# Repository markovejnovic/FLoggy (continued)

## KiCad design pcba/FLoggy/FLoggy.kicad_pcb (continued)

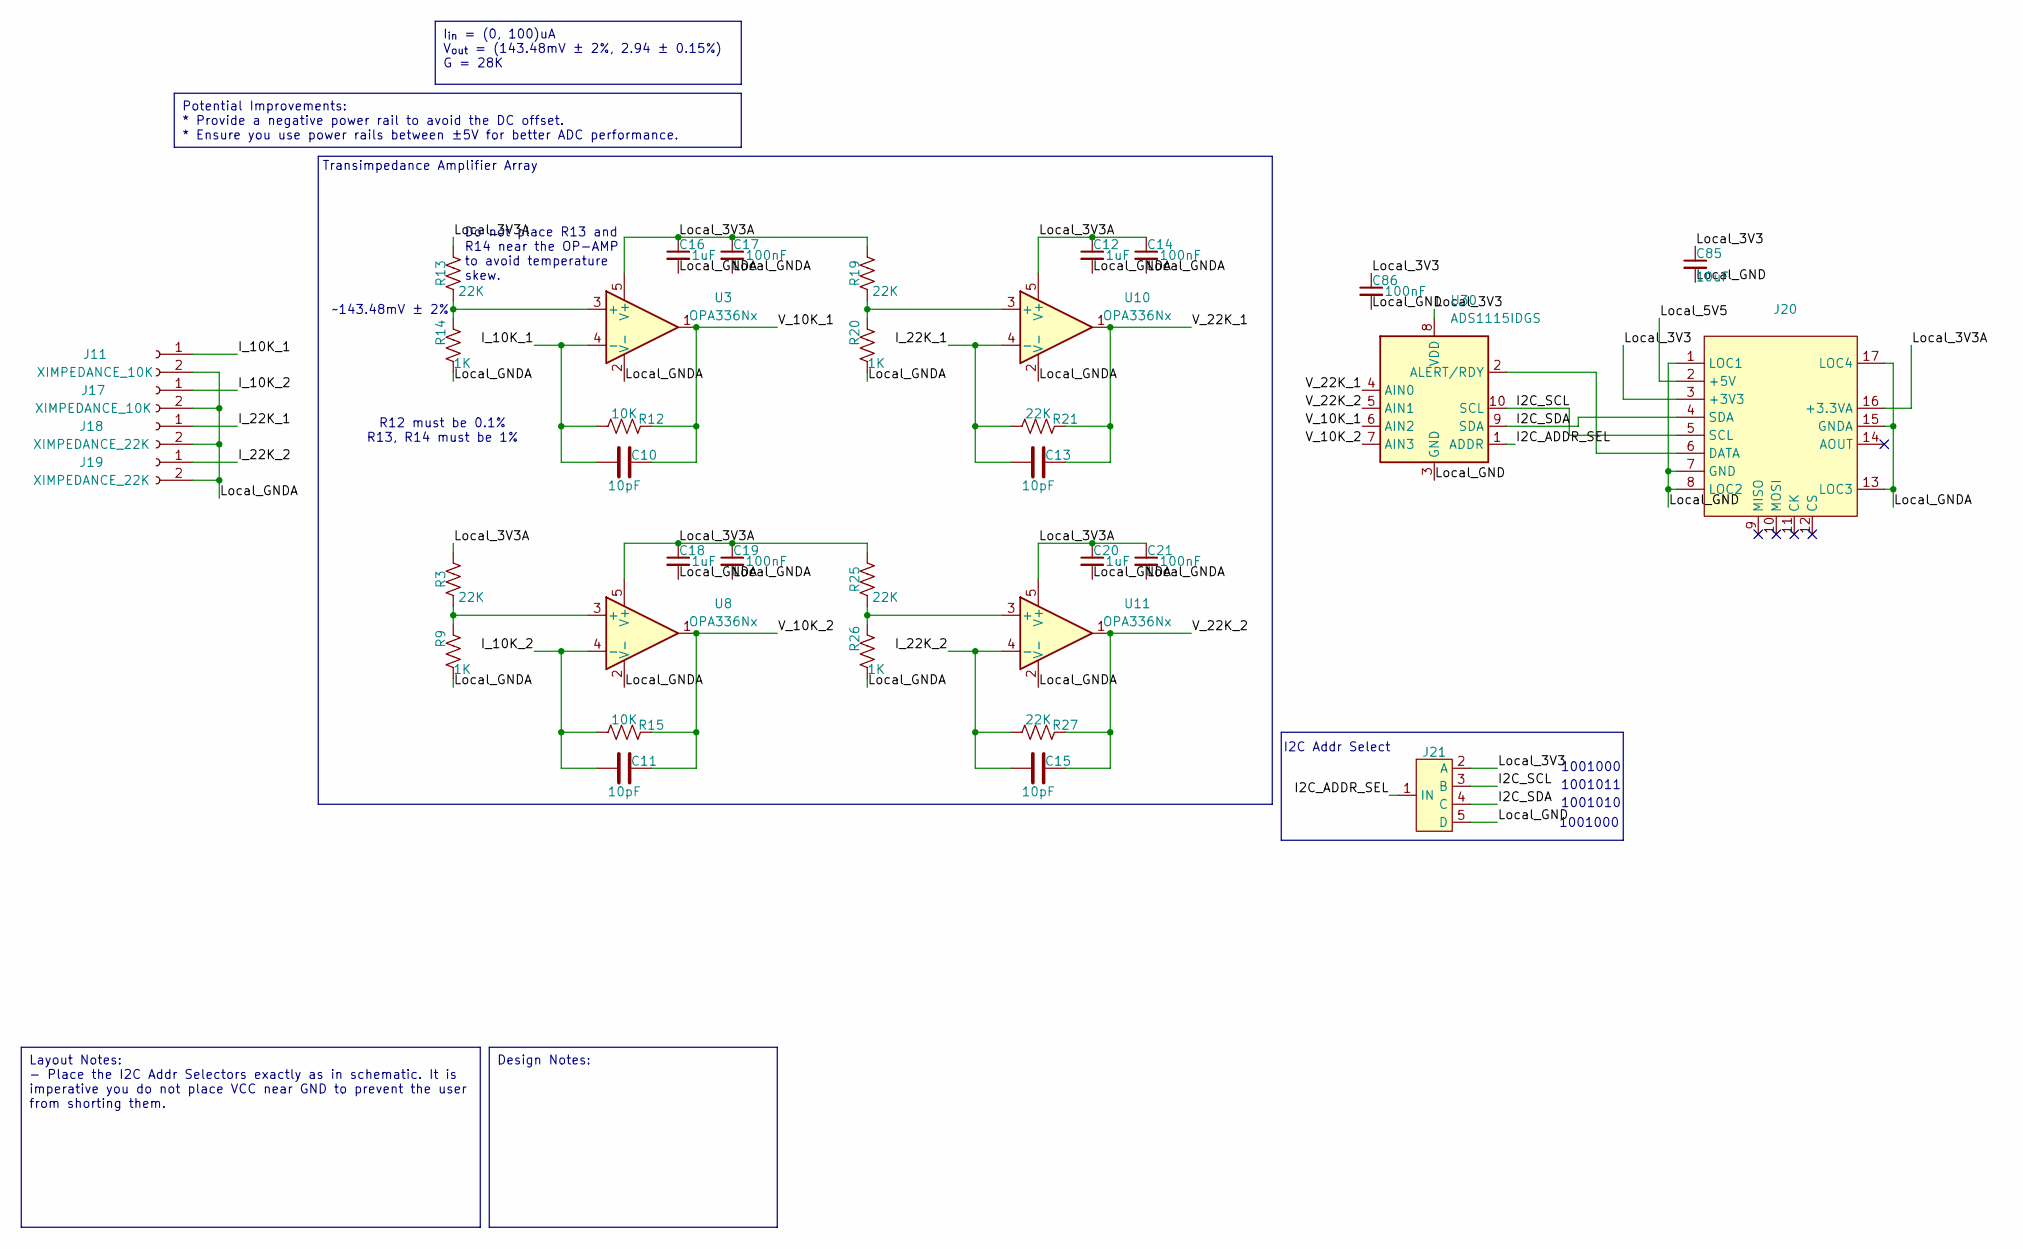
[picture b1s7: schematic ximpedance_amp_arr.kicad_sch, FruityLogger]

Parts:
C10, C11, C13, C15: 10pF; C_0603_1608Metric; JLCPCB Basic? True
C12, C16, C18, C20: 1uF; C_0805_2012Metric; JLCPCB Basic? True
C14, C17, C19, C21, C86: 100nF; C_0603_1608Metric; JLCPCB Basic? True
C85: 10uF; C_0805_2012Metric; JLCPCB Basic? True
J11, J17: XIMPEDANCE_10K; TerminalBlock_Phoenix_MPT-0,5-2-2.54_1x02_P2.54mm_Horizontal
J18, J19: XIMPEDANCE_22K; TerminalBlock_Phoenix_MPT-0,5-2-2.54_1x02_P2.54mm_Horizontal
J20: FloggyModuleShield
J21: I2C Addr Picker
R3, R13, R19, R21, R25, R27: 22K; R_0603_1608Metric; JLCPCB Basic? True
R9, R14, R20, R26: 1K; R_0603_1608Metric; JLCPCB Basic? True
R12, R15: 10K; R_0603_1608Metric; JLCPCB Basic? True
U3, U8, U10, U11: OPA336Nx; SOT-23-5; JLCPCB Basic? False
U30: ADS1115IDGS; TSSOP-10_3x3mm_P0.5mm

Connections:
/Transimpedance Amplifier Array Breakout/I2C_ADDR_SEL: J21.1 (IN), U30.1 (ADDR)
/Transimpedance Amplifier Array Breakout/I2C_SCL: J20.5 (SCL), J21.3 (B), U30.10 (SCL)
/Transimpedance Amplifier Array Breakout/I2C_SDA: J20.4 (SDA), J21.4 (C), U30.9 (SDA)
/Transimpedance Amplifier Array Breakout/I_10K_1: C10.1, J11.1, R12.1, U3.4 (-)
/Transimpedance Amplifier Array Breakout/I_10K_2: C11.1, J17.1, R15.1, U8.4 (-)
/Transimpedance Amplifier Array Breakout/I_22K_1: C13.1, J18.1, R21.1, U10.4 (-)
/Transimpedance Amplifier Array Breakout/I_22K_2: C15.1, J19.1, R27.1, U11.4 (-)
/Transimpedance Amplifier Array Breakout/Local_3V3: C85.1, C86.1, J20.3 (+3V3), J21.2 (A), U30.8 (VDD)
/Transimpedance Amplifier Array Breakout/Local_3V3A: C12.1, C14.1, C16.1, C17.1, C18.1, C19.1, C20.1, C21.1, J20.16 (+3.3VA), R3.2, R13.2, R19.2, R25.2, U3.5 (V+), U8.5 (V+), U10.5 (V+), U11.5 (V+)
/Transimpedance Amplifier Array Breakout/Local_5V5: J20.2 (+5V)
/Transimpedance Amplifier Array Breakout/Local_GND: C85.2, C86.2, J20.1 (LOC1), J20.7 (GND), J20.8 (LOC2), J21.5 (D), U30.3 (GND)
/Transimpedance Amplifier Array Breakout/Local_GNDA: C12.2, C14.2, C16.2, C17.2, C18.2, C19.2, C20.2, C21.2, J11.2, J17.2, J18.2, J19.2, J20.13 (LOC3), J20.15 (GNDA), J20.17 (LOC4), R9.1, R14.1, R20.1, R26.1, U3.2 (V-), U8.2 (V-), U10.2 (V-), U11.2 (V-)
/Transimpedance Amplifier Array Breakout/V_10K_1: C10.2, R12.2, U3.1, U30.6 (AIN2)
/Transimpedance Amplifier Array Breakout/V_10K_2: C11.2, R15.2, U8.1, U30.7 (AIN3)
/Transimpedance Amplifier Array Breakout/V_22K_1: C13.2, R21.2, U10.1, U30.4 (AIN0)
/Transimpedance Amplifier Array Breakout/V_22K_2: C15.2, R27.2, U11.1, U30.5 (AIN1)
unnamed: J20.6 (DATA), U30.2 (ALERT/RDY)
unnamed: R13.1, R14.2, U3.3 (+)
unnamed: R3.1, R9.2, U8.3 (+)
unnamed: R19.1, R20.2, U10.3 (+)
unnamed: R25.1, R26.2, U11.3 (+)

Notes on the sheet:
Potential Improvements: * Provide a negative power rail to avoid the DC offset. * Ensure you use power rails between ±5V for better ADC performance.
I_{in} = (0, 100)uA V_{out} = (143.48mV ± 2%, 2.94 ± 0.15%) G = 28K
Layout Notes: - Place the I2C Addr Selectors exactly as in schematic. It is imperative you do not place VCC near GND to prevent the user from shorting them.
Design Notes:
Do not place R13 and R14 near the OP-AMP to avoid temperature skew.
~143.48mV ± 2%
Transimpedance Amplifier Array
1001010
1001000
R12 must be 0.1% R13, R14 must be 1%
I2C Addr Select
1001011

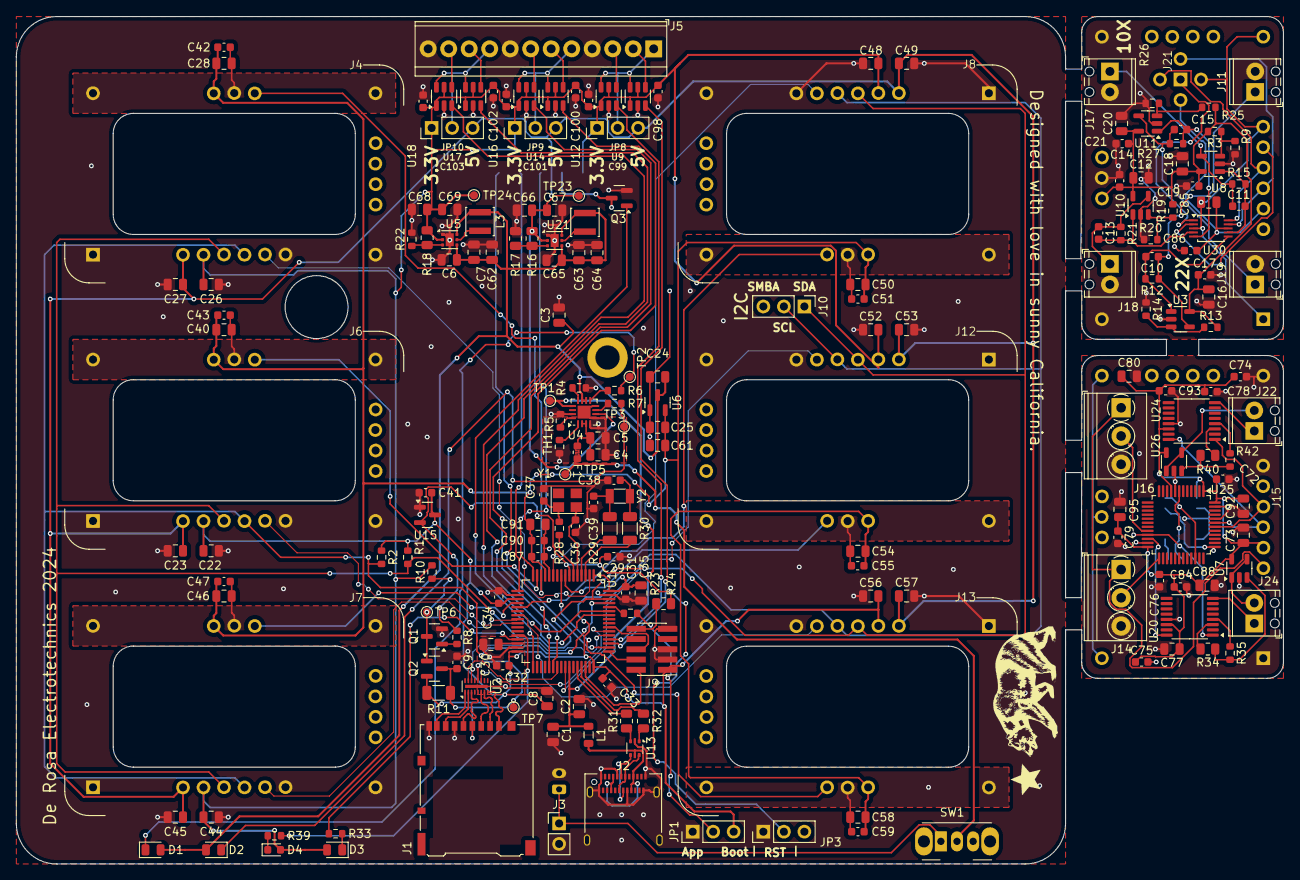
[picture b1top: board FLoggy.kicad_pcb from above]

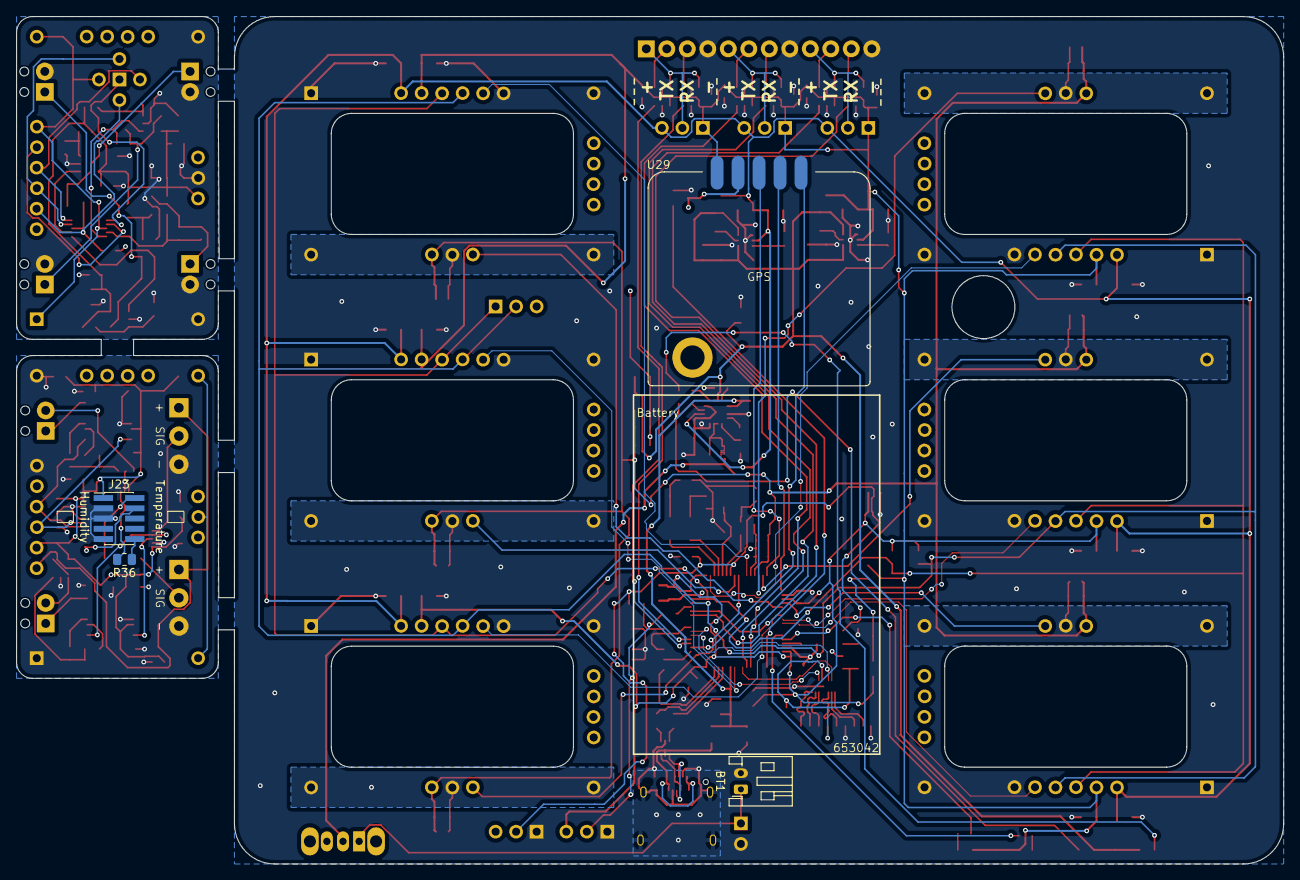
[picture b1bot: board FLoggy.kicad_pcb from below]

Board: 4 copper layers, 157.0 x 105.0 mm, 210 parts (4 on the bottom side), 137 nets.

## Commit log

2024-06-06 Initial PCBA Commit
